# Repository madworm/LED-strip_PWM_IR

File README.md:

LED_port-status
===============

LAYOUT FILES: Small high-current PWM controller with IR receiver (ATtiny85 based). 

---

Before having PC-boards made, please make sure you know about your manufacturer's peculiarities!
Especially drill-sizes and their tolerances may vary too much and give you trouble.

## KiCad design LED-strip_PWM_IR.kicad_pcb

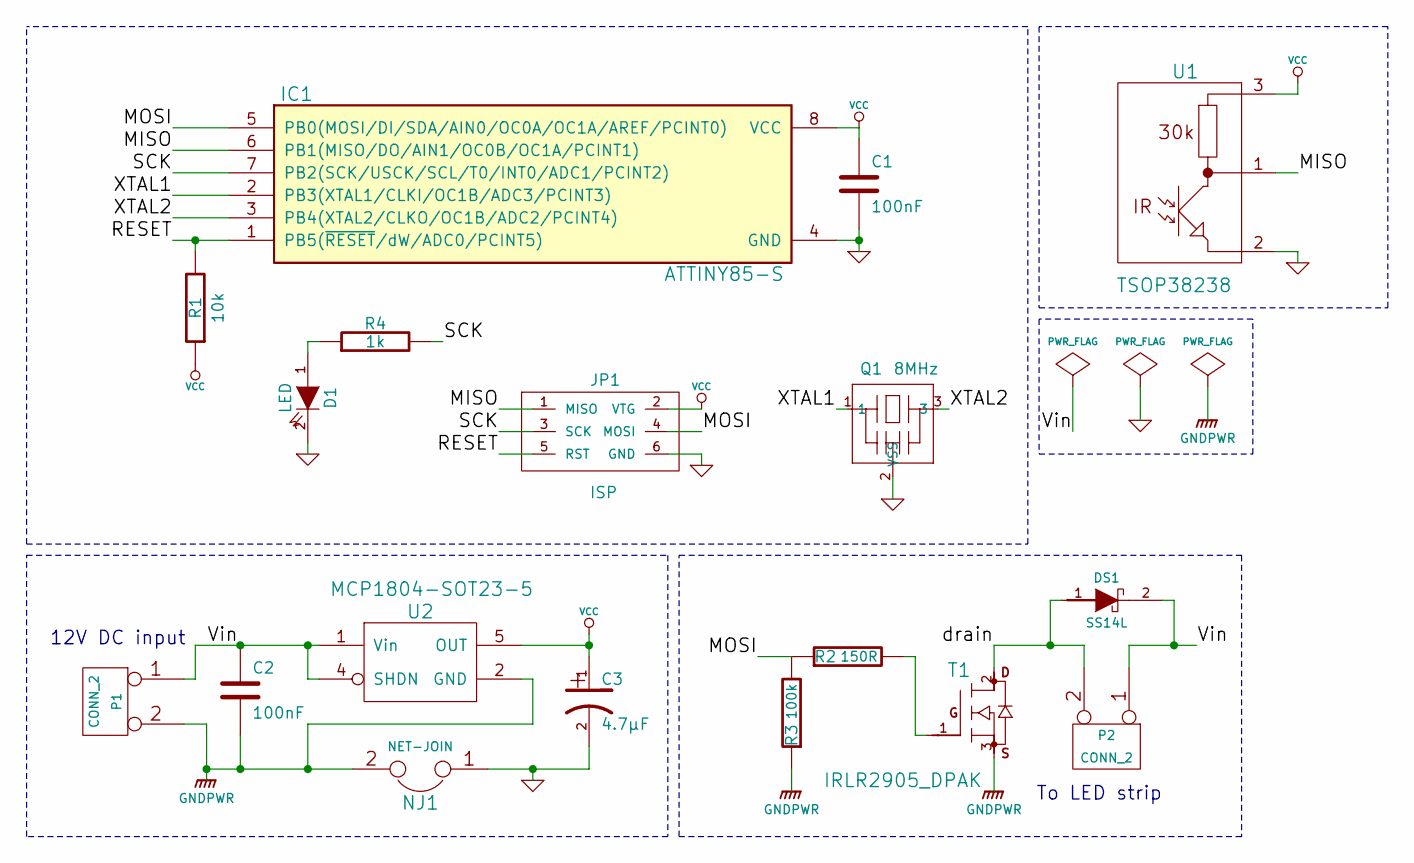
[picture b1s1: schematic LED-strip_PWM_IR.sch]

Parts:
C1, C2: 100nF
C3: 4.7µF
D1: LED
DS1: SS14L
IC1: ATTINY85-S
JP1: ISP
NJ1: NET-JOIN
P1, P2: CONN_2
Q1: 8MHz
R1: 10k
R2: 150R
R3: 100k
R4: 1k
T1: IRLR2905_DPAK
U1: TSOP38238
U2: MCP1804-SOT23-5

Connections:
/MISO: IC1.6 (PB1(MISO/DO/AIN1/OC0B/OC1A/PCINT1)), JP1.1 (MISO), U1.1
/MOSI: IC1.5 (PB0(MOSI/DI/SDA/AIN0/OC0A/OC1A/AREF/PCI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), JP1.4 (MOSI), R2.1, R3.2
/RESET: IC1.1 (PB5(~RESET~/dW/ADC0/PCINT5)), JP1.5 (RST), R1.2
/SCK: IC1.7 (PB2(SCK/USCK/SCL/T0/INT0/ADC1/PCINT2)), JP1.3 (SCK), R4.2
/Vin: C2.1, DS1.2 (C), P1.1, P2.1, U2.1 (Vin), U2.4 (SHDN)
/XTAL1: IC1.2 (PB3(XTAL1/CLKI/OC1B/ADC3/PCINT3)), Q1.1
/XTAL2: IC1.3 (PB4(XTAL2/CLKO/OC1B/ADC2/PCINT4)), Q1.3
/drain: DS1.1 (A), P2.2 (PM), T1.2 (D)
GND: C1.2, C3.2, D1.2 (K), IC1.4 (GND), JP1.6 (GND), NJ1.1, Q1.2 (VSS), U1.2
GNDPWR: C2.2, NJ1.2, P1.2 (PM), R3.1, T1.3 (S), U2.2 (GND)
unnamed: D1.1 (A), R4.1
unnamed: R2.2, T1.1 (G)
VCC: C1.1, C3.1, IC1.8 (VCC), JP1.2 (VTG), R1.1, U1.3, U2.5 (OUT)

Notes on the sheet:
To LED strip
12V DC input

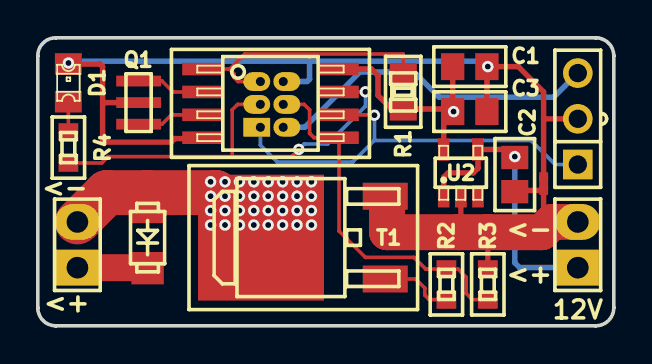
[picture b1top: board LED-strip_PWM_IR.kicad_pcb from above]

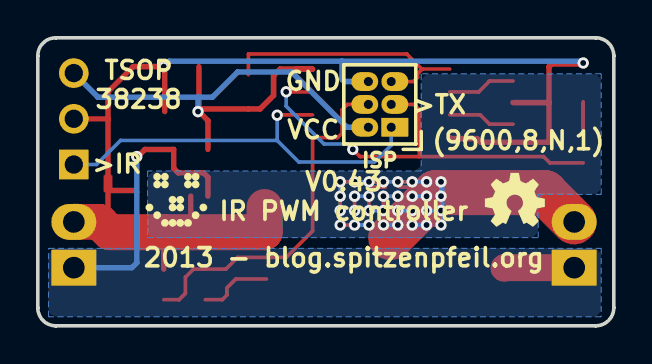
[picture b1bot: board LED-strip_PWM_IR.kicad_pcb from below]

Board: 2 copper layers, 32.0 x 16.0 mm, 20 parts (3 on the bottom side), 13 nets.

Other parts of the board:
G1: LOGO
G2: LOGO

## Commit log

2012-11-25 Logic GND was sharing a high-current path. Fixed.
2012-11-25 Flipped IN/OUT connectors (less copper) + bigger holes.
2012-11-25 Replaced: TO-252 footprint with a custom one (larger pads) + tweaks.
2012-11-25 FET resistor --> 0603 + new place.
2012-11-26 Changed IRLR2905 gate resistor to 150R.
2012-11-26 Recreated changed PNGs.
2012-11-27 Added bottom copper zone as heatsink for the MOSFET.
2012-11-27 Fixed murata resonator (CSTCC) footprint.
2012-11-27 Added a 20k gate pull-down.
2012-11-28 Shifted vias to stay clear of the back heatsink copper zone.
2012-11-28 Moved board to align with a 1mm grid.
2012-12-01 Tweaks.
2013-01-07 Added README.md
2013-01-08 Fixed the ATtiny85 footprint issue.
2013-01-08 Removed 'README.md'
2013-01-08 Silkscreen tweaks.
2013-01-09 Replaced 78L05 with MCP1804-SOT23 (low drop). Board-shrink.
2013-01-09 B-Silkscreen fixed.
2013-01-09 Updated make_all-pngs.sh
2013-01-09 Added a LED as IR reception indicator (optional).
2013-01-09 Increased the drill-size for the TSOP38328 to 40mil.
2013-01-09 Adapted to the changed MCP1804-SOT23-5 schematic symbol.
    No changes to the board layout itself, only behind the scenes stuff.
2013-01-12 Shoved some parts around, maybe it looks nicer now. Maybe not...
2013-01-13 Power traces: 8mil --> 12mil.
2013-01-15 Tweaked b-silkscreen.
2013-01-16 Silkscreen tweaks + removed all (via-in-pad)s.
2013-01-16 Bord shrink to 25x20mm.
2013-01-20 Added a comments layer with board dimensions.
2013-01-26 Replaced the jumper with a real net-tie footprint.
2013-01-27 Switched to REV. 202 of atmel.lib
2013-01-27 Wrong LED footprint. Was 0603, should've been 0805. GAH!
2013-02-09 Changed MCP1804 footprint: SOT23-5 --> SOT23-5L
2013-02-09 Increased pad-size of headers for wider annular ring + small tweaks.
2013-02-12 Moved the LED to the left side of the board, away from the IR receiver.
2013-02-12 Changed the resonator type: CSTCC --> CSTCE. About 1/2 the size.
2013-02-13 Moved footprints --> board shrunk by 1mm in height.
2013-02-13 Larger pads for the new CSTCE oscillator. Hand soldering...
2013-02-15 Added some artwork to the back side ;-)
2013-05-14 Updated 'README.md'
2013-05-17 Added a protection Schottky-Diode for the MOSFET. Now V0.3
2013-05-19 Re-spun the board again: square shape --> oblong shape.
2013-05-19 Recrated gerber-files + PNGs.
2013-05-19 Grmbl! Never trust footprints from 'some lib'...
2013-05-19 Recreated gerber-files.
2013-05-19 Recrated PNGs.
2013-05-19 Fixed a brain-fart... Why use a direct trace, if you can use lots of vias?
2013-05-20 Updated .gitignore file.
2013-05-24 Added heat-sink copper-pour with lots of vias again. Board-Rev. 0.42
2013-06-16 Switched Schottky diode to SS14L + rounded corners.
2013-09-29 Fixed resonator footprint (library part was off).
